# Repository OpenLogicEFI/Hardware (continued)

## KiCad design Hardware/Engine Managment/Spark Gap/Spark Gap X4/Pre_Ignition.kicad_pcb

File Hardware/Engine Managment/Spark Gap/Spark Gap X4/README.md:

# Spark Gap

Spark Gap x4 is an open-source, universal standalone engine management system designed
for the budget-minded enthusiast seeking a comprehensive all-in-one solution.
It is compact and feature-rich, utilizing an off-the-shelf case and connector.

Board Selection in tuner studio for this ECU is "Speeduino v0.4"

RevA: Initial Release 2024
RevB: Never released
RevC: Released 2025

www.OpenLogicEFI.com

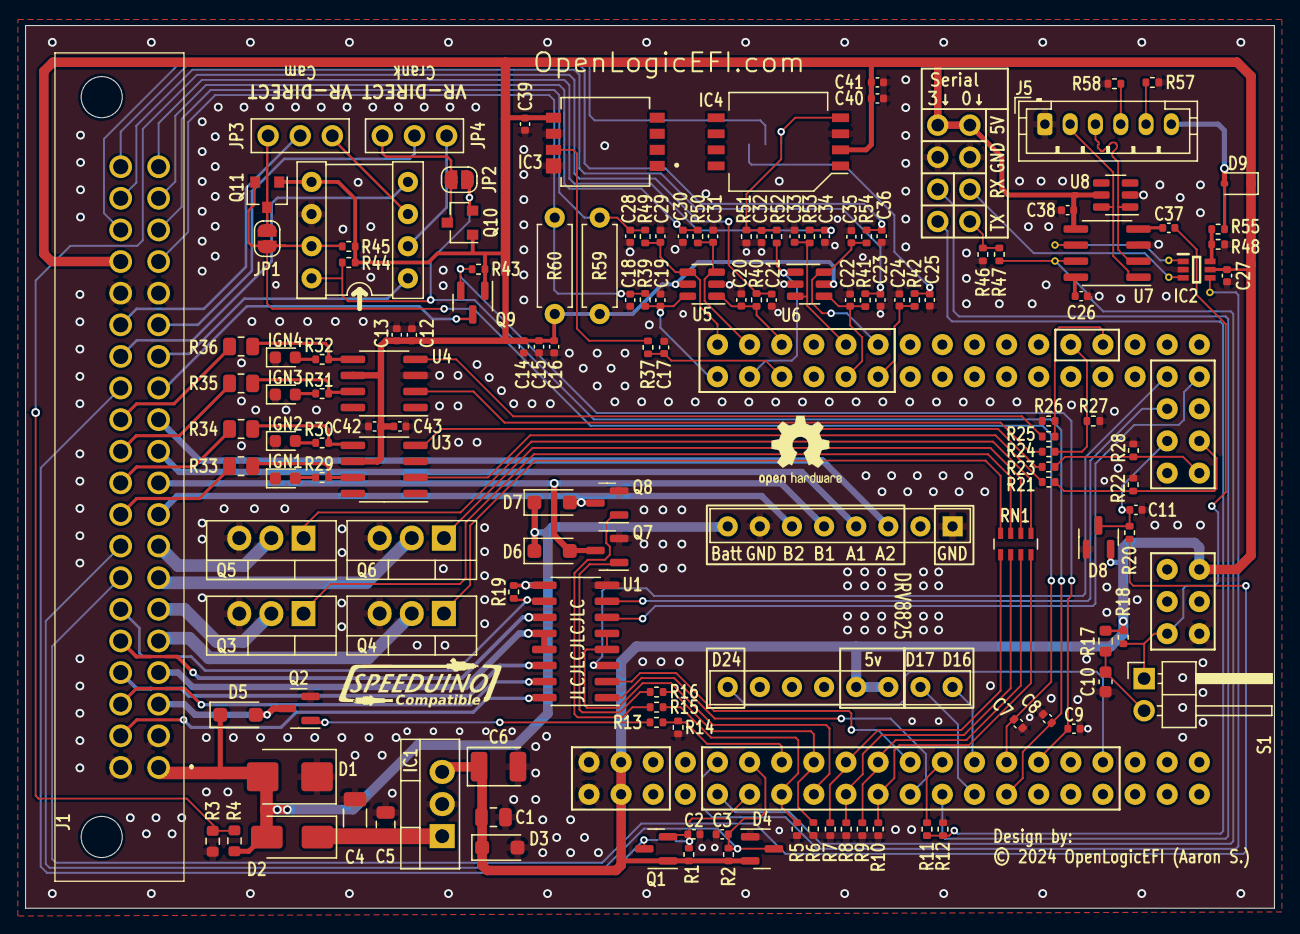
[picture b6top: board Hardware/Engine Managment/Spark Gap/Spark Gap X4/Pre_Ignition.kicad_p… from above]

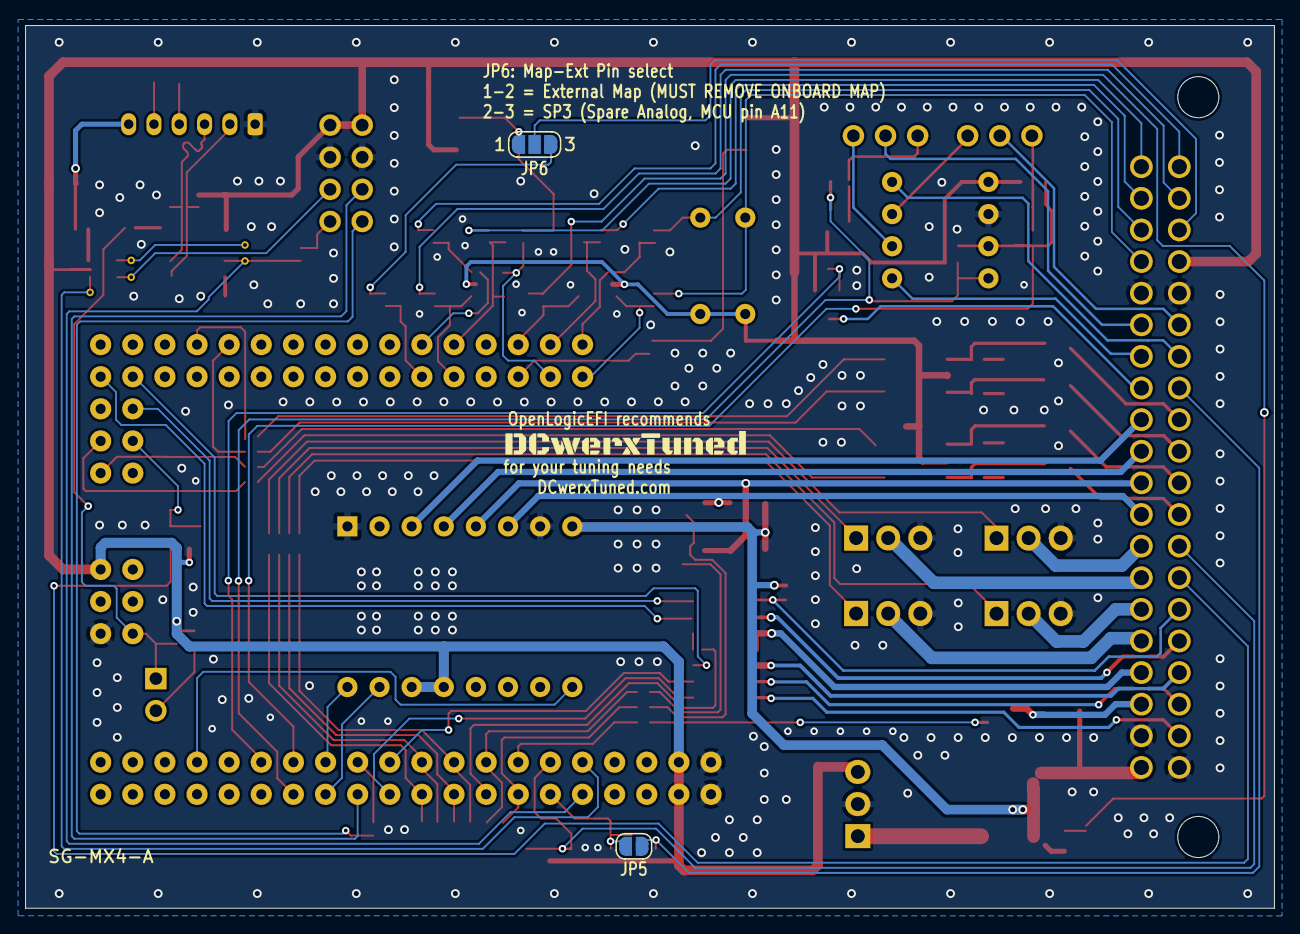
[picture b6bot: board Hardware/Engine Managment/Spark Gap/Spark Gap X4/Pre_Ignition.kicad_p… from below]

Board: 2 copper layers, 98.8 x 69.8 mm, 158 parts (2 on the bottom side), 118 nets.

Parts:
A1: DRV8825_Module; DVR8825-Labeled-Front
C1: 100nF; C_0805_2012Metric
C2, C8, C9: 10nF; C_0402_1005Metric
C3, C11, C15, C19, C20, C22, C24, C29, C31, C33, C35: 220nF; C_0402_1005Metric
C4: 2.2uF; C_1206_3216Metric
C5: 470nF; C_0805_2012Metric
C6: 100uF; CP_EIA-3528-15_AVX-H
C7, C12, C14, C17, C18, C21, C23, C25, C26, C27, C28, C30, C34, C36, C37, C38, C39, C40, C43: 100nF; C_0402_1005Metric
C10: 10uF; C_0603_1608Metric
C13, C16, C41, C42: 1uF; C_0402_1005Metric
C32: 47pF; C_0402_1005Metric
D1: SMBJ30CA; D_SMB
D2: M7; D_SMA
D3: SMF6V0CA; D_SOD-123F
D4, D8: BAV99; SOT-23
D5, D6, D7: SM4007PL; D_SOD-123F
D9: 1N5819WS; D_SOD-323
G1: Logo_Open_Hardware_Small; SpeeduinoCompatible-14mm
G2: Logo_Open_Hardware_Small; OSHW-Logo2_7.3x6mm_SilkScreen
IC1: LM2940; TO-220-3_Vertical
IC2: 74LVC1G157GW,125; SOP65P210X110-6N
IC3: KP234XTMA1; KP234
IC4: MPXHZ6400; MPXH6250
IGN1, IGN2, IGN3, IGN4: LED; LED_0603_1608Metric
J1: MX23A40NF1
J2: VR_Header; Socket_VRConditioner_Corrected
J3, J4: Conn_01x04; 1X4-PROTO-NoSilk
J5: USB-S0; JST_PH_B6B-PH-K_1x06_P2.00mm_Vertical
JP1, JP2, JP5: FET Bypass; SolderJumper-2_P1.3mm_Open_RoundedPad1.0x1.5mm
JP3, JP4: DIRECT/VR; 1x03-Proto
JP6: SolderJumper_3_Open; SolderJumper-3-OPEN
Q1, Q2, Q7, Q8, Q9, Q10, Q11: AO3400A; SOT-23
Q3, Q4, Q5, Q6: STP75N04Z; TO-220-3_Vertical
R1, R11, R20, R21, R23, R24, R25, R43, R44, R45, R47: 1k; R_0402_1005Metric
R2: 2.4k; R_0402_1005Metric
R3: 1k; R_0603_1608Metric
R4: 3.9k; R_0603_1608Metric
R5, R6, R7, R8, R9, R10, R14, R22, R26, R27, R28: 100k; R_0402_1005Metric
R12, R46: 2k; R_0402_1005Metric
R13, R15, R16, R29, R30, R31, R32, R39, R40, R41, R42, R49, R50, R52, R53, R54, R55: 470r; R_0402_1005Metric
R17: 120r; R_0603_1608Metric
R18, R19, R48: 10k; R_0402_1005Metric
R33, R34, R35, R36: 22; R_0805_2012Metric
R37, R51: 51k; R_0402_1005Metric
R57, R58: 5.1k; R_0402_1005Metric
R59, R60: 2.49k; R_Axial_DIN0207_L6.3mm_D2.5mm_P7.62mm_Horizontal
RN1: 1k; R_Array_Concave_4x0603
S1: Reset Control; PinHeader_1x02_P2.54mm_Horizontal
TP1, TP2, TP3, TP4, TP5: TestPoint; TestPoint_THT_D0.6mm_Drill0.3mm
U1: ULN2003ADR; SOIC-16_3.9x9.9mm_P1.27mm
U2: Mega_Pro_VinPinsUnpopulated; Arduino_Mega_Mini_2560_SmallCrtYd_NoVin
U3, U4: TC4424; SOIC-8_3.9x4.9mm_P1.27mm
U5, U6, U8: SRV05-4-P-T7; SOT-23-6
U7: CH340N; SOIC-8_3.9x4.9mm_P1.27mm

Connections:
+5V: A1.13 (~RST), A1.14 (~SLP), C1.1, C6.1, C12.1, C13.1, C14.1, C15.1, C16.1, C27.2, C38.1, C39.1, C40.1, C41.1, C42.1, C43.1, D3.1 (A1), D4.2 (A), D8.2 (A), D9.1 (K), IC1.3 (OUT), IC2.5 (VCC), IC3.5 (VDD), IC4.2 (VS), J1.37, J2.5, J3.1, J4.1, Q1.1 (G), Q9.1 (G), Q10.1 (G), Q11.1 (G), R1.1, R2.2, R17.2, R18.1, R43.1, R44.1, R45.1, R59.1, R60.2, U2.5V_1 (5V), U2.5V_2 (5V), U2.5V_3 (5V), U3.6 (V+), U4.6 (V+), U5.5 (REF), U6.5 (REF), U7.5 (VCC), U8.5 (REF)
+BATT: A1.8 (VMOT), D1.2 (A2), D2.2 (A), D5.1 (K), D6.1 (K), D7.1 (K), J1.1, R4.2, R19.2, U1.9 (COM)
ADC1: C23.1, J1.39, R41.2
ADC2: C36.1, J1.40, R54.2
ADC3: C25.1, JP6.3 (B), R42.2
BOOST: J1.4, U1.12 (O5), U1.13 (O4)
BaroIn: IC3.7 (VOUT), R37.1
CH340-TX0: IC2.1 (I1), TP4.1, TP5.1, U7.6 (RXD)
CLT: C18.1, J1.17, R39.2, R60.1
Cam2: J1.33, JP5.1 (A), Q1.3 (D)
Cam-In: J1.35, JP3.2
Clutch: J1.27, R20.2
Crank-In: J1.15, JP4.2
D12-OUT: J1.23, U1.15 (O2)
D13-OUT: J1.22, U1.16 (O1)
D+: J5.2, U7.1 (UD+), U8.6 (I/O_4)
D-: J5.3, U7.2 (UD-), U8.1 (I/O_1)
Fan: J1.25, U1.11 (O6)
Flex: C3.1, D4.3 (K), J1.28, R2.1, U2.D2
Fuel-Pump: J1.24, U1.14 (O3)
GND: A1.1 (GND), A1.7 (GND), C1.2, C2.1, C3.2, C4.2, C5.2, C6.2, C7.1, C8.1, C9.2, C10.2, C11.2, C12.2, C13.2, C14.2, C15.2, C16.2, C17.2, C18.2, C19.2, C20.2, C21.2, C22.2, C23.2, C24.2, C25.2, C26.2, C27.1, C28.2, C29.2, C30.2, C31.2, C32.2, C33.2, C34.2, C35.2, C36.2, C38.2, C39.2, C40.2, C41.2, C42.2, C43.2, D1.1 (A1), D3.2 (A2), D4.1 (K), D8.1 (K), IC1.2 (GND), IC2.2 (GND), IC3.6 (GND), IC3.8 (GND), IC4.3 (GND), IGN1.1 (K), IGN2.1 (K), IGN3.1 (K), IGN4.1 (K), J1.2, J1.16, J1.21, J1.36, J2.6, J3.2, J4.2, J5.1, Q2.2 (S), Q3.3 (S), Q4.3 (S), Q5.3 (S), Q6.3 (S), Q7.2 (S), Q8.2 (S), R3.1, R5.1, R6.1, R7.1, R8.1, R9.1, R10.1, R12.2, R14.1, R22.1, R26.1, R27.1, R28.1, R46.2, R48.1, R51.1, R57.2, R58.2, U1.8 (GND), U2.GND_1 (GND), U2.GND_2 (GND), U2.GND_3 (GND), U3.3 (GND), U4.3 (GND), U5.2 (GND), U6.2 (GND), U7.3 (GND), U8.2 (GND)
IAT: C28.1, J1.18, R49.2, R59.2
IDLE1: A1.6 (B2), D7.2 (A), J1.9, Q8.3 (D)
IDLE2: A1.5 (B1), D6.2 (A), J1.10, Q7.3 (D)
IGN1: J1.32, R36.1
IGN2: J1.31, R35.1
IGN3: J1.30, R34.1
IGN4: J1.29, R33.1
INJ1: J1.5, Q4.2 (D)
INJ2: J1.6, Q3.2 (D)
INJ3: J1.7, Q6.2 (D)
INJ4: J1.8, Q5.2 (D)
MC-A0: C29.1, R49.1, U2.A0, U5.4 (I/O_3)
MC-A1: C19.1, R39.1, U2.A1, U5.6 (I/O_4)
MC-A2: C31.1, R50.1, U2.A2, U5.3 (I/O_2)
MC-A3: R52.2, U2.A3, U6.1 (I/O_1)
MC-A4: C20.1, R40.1, U2.A4, U5.1 (I/O_1)
MC-A5: C17.1, R37.2, U2.A5
MC-A8: C33.1, R53.1, U2.A8, U6.3 (I/O_2)
MC-A9: C22.1, R41.1, U2.A9, U6.4 (I/O_3)
MC-A10: C35.1, R54.1, U2.A10, U6.6 (I/O_4)
MC-A11: C24.1, R42.1, U2.A11
MC-D3: C2.2, JP5.2 (B), Q1.2 (S), R1.2, U2.D3
MC-D4: R13.1, R14.2, U2.D4
MC-D5: R5.2, R15.1, U2.D5
MC-D6: R6.2, R16.1, U2.D6
MC-D7: U1.4 (I4), U1.5 (I5), U2.D7
MC-D8: R7.2, RN1.5 (R4.2), U2.D8
MC-D9: R8.2, RN1.6 (R3.2), U2.D9
MC-D10: R9.2, RN1.7 (R2.2), U2.D10
MC-D11: R10.2, RN1.8 (R1.2), U2.D11
MC-D12: U1.2 (I2), U2.D12
MC-D13: U1.1 (I1), U2.D13
MC-D14-TX3: R11.1, U2.D14
MC-D15-RX3: J3.3, U2.D15
MC-D16: A1.16 (DIR), U2.D16
MC-D17: A1.15 (STEP), U2.D17
MC-D18: C7.2, J2.7, JP1.2 (B), Q11.2 (S), R45.2, U2.D18
MC-D19: C8.2, J2.8, JP2.2 (B), Q10.2 (S), R44.2, U2.D19
MC-D20: C9.1, Q9.2 (S), R43.2, U2.D20
MC-D24: A1.9 (~EN), U2.D24
MC-D38: R24.1, R27.2, U2.D38
MC-D40: R25.1, R26.2, U2.D40
MC-D45: U1.3 (I3), U2.D45
MC-D47: U1.6 (I6), U2.D47
MC-D49: U1.7 (I7), U2.D49
MC-D50: R21.1, R22.2, U2.D50
MC-D51: C11.1, D8.3 (K), R20.1, U2.D51
MC-D52: R23.1, R28.2, U2.D52
MC-RESET: C37.2, R18.2, S1.1, U2.RESET
MC-RX0: IC2.4 (Y), TP1.1, U2.RX
MC-TX0: R47.1, TP3.1, U2.TX, U7.7 (TXD)
Map-Ext: J1.38, JP6.2 (C)
MapIn: C32.1, IC4.4 (VOUT), JP6.1 (A), R51.2, R52.1
unnamed: C21.1, R3.2, R4.1, R40.2
unnamed: C4.1, C5.1, D2.1 (K), IC1.1 (IN)
unnamed: IC2.6 (S), R48.2, R55.1
unnamed: IGN1.2 (A), R29.2
unnamed: IGN2.2 (A), R30.2
unnamed: IGN3.2 (A), R31.2
unnamed: IGN4.2 (A), R32.2
unnamed: J3.4, R11.2, R12.1
unnamed: J4.4, R46.1, R47.2
unnamed: J5.4, R58.1
unnamed: J5.5, R57.1
unnamed: JP1.1 (A), JP3.1, Q11.3 (D)
unnamed: JP2.1 (A), JP4.1, Q10.3 (D)
unnamed: Q2.1 (G), R13.2
unnamed: Q3.1 (G), RN1.3 (R3.1)
unnamed: Q4.1 (G), RN1.4 (R4.1)
unnamed: Q5.1 (G), RN1.1 (R1.1)
unnamed: Q6.1 (G), RN1.2 (R2.1)
unnamed: Q7.1 (G), R16.2
unnamed: Q8.1 (G), R15.2
unnamed: C10.1, R17.1, S1.2
unnamed: R21.2, U3.2 (IN_A)
unnamed: R23.2, U3.4 (IN_B)
unnamed: R29.1, R33.2, U3.7 (OUT_A)
unnamed: R30.1, R34.2, U3.5 (OUT_B)
unnamed: R24.2, U4.2 (IN_A)
unnamed: R25.2, U4.4 (IN_B)
unnamed: R31.1, R35.2, U4.7 (OUT_A)
unnamed: R32.1, R36.2, U4.5 (OUT_B)
unnamed: C26.1, U7.8 (V3)
unnamed: C37.1, U7.4 (~RTS)
O2: C34.1, J1.20, R53.2
S0-TX-Proto: IC2.3 (I0), J4.3, TP2.1
Step-A1: A1.4 (A1), J1.11
Step-A2: A1.3 (A2), J1.12
TPS: C30.1, J1.19, R50.2
Tach: J1.26, R19.1, U1.10 (O7)
VBus: D9.2 (A), J5.6, R55.2
VR1+: J2.2, JP4.3
VR1-: J1.14, J2.1
VR2+: J2.3, JP3.3
VR2-: J1.34, J2.4
VSS: J1.13, Q9.3 (D)
VVT: D5.2 (A), J1.3, Q2.3 (D)
